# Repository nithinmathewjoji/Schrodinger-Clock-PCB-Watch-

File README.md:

# Schrödinger Clock - Open Source Smartwatch (Prototype⚠️)

<p align="center">Sponsored By </p>
<p align="center">
  
</p>

*A compact, open-source smartwatch powered by the ESP32-S3-WROOM with real-time clock, battery monitoring, and USB charging.*

---

## 📑 Index

1. [Introduction](#introduction)
2. [Features](#features)
3. [Hardware Overview](#hardware-overview)
4. [Sponsorship and Support](#Sponsorship-and-Support)
5. [Schematic & PCB Design](#schematic--pcb-design)
6. [Known issues & Fix](#Known-issues-and-Fix)
7. [Bill of Materials (BoM)](#bill-of-materials-bom)
8. [Firmware & Software](#firmware--software)
9. [Assembly & Soldering Guide](#assembly--soldering-guide)
10. [Usage Guide](#usage-guide)
11. [Power Management](#power-management)
12. [Downloads](#downloads)
13. [Firmware](#firmware)
14. [Visit Interactive BOM](https://nithinmathewjoji.github.io/Schrodinger-Clock-PCB-Watch-/)
15. [Contributing](#contributing)
16. [License](#license)
17. [Acknowledgments](#acknowledgments)

---

## Introduction

The **Schrödinger Watch** is an ESP32-S3-based open-source smartwatch designed with a focus on **compact PCB layout**, **low power consumption**, and **modular features**. It integrates **RTC, I2C display, battery monitoring**, and a **USB charging circuit**, making it a versatile platform for wearable tech enthusiasts.

---

## Features

| Feature                  | Description |
|--------------------------|-------------|
| **Microcontroller**      | ESP32-S3-WROOM (40-pin) |
| **Display**              | I2C OLED |
| **RTC Module**          | DS3231 (with alarm) |
| **Buttons**              | 3 push buttons (pull-up) |
| **Buzzer**               | Included for alarms and notifications |
| **Battery**              | 3.7V Li-Po battery |
| **Charging Circuit**     | TP4056 for Li-Po charging |
| **Battery Monitoring**   | Voltage divider for ADC measurement |
| **USB Communication**    | CP2102 USB programmer |
| **Power Switching**      | *P-MOSFET for auto power control |
| **Protection Circuit**   | Schottky diode for USB protection |

* *feature will be added on the next revision
---

## Hardware Overview

The smartwatch is designed with **SMD components** for compactness. Below is the pin mapping:

| Component   | ESP32 GPIO | Function |
|------------|------------|----------|
| OLED SDA   | GPIO 20   | I2C SDA  |
| OLED SCL   | GPIO 21   | I2C SCL  |
| RTC SDA   | GPIO 20   | I2C SDA  |
| RTC SCL   | GPIO 21   | I2C SCL  |
| RTC Alarm  | GPIO 11 | SQW/INT to ESP32 |
| Battery ADC | GPIO7 | Voltage divider to ESP32 Analog Pin |
| LED        | GPIO 2    | Status Indication |
| LED        | GPIO 3    | Status Indication |
| LED        | GPIO 4    | Status Indication |
| Push Button 1 | GPIO 12  | User Input |
| Push Button 2 | GPIO 13 | User Input |
| Push Button 3 | GPIO 22  | User Input |

* refer circuit  [Schrödinger_Watch_schematics](https://github.com/nithinmathewjoji/Schrodinger-Clock-PCB-Watch-/blob/master/Schematics/schematic.pdf) for more detailed pin out.and pin assignments

---

## Sponsorship and Support

<p align="center">
  
</p>

### 🙏 Thank You, PCBWay!

This project was proudly sponsored by [**PCBWay**](https://pcbway.com/g/D6Z94Y).  

Their support in fabricating the custom PCB for the Schrödinger Watch has been invaluable. The quality, precision, and delivery speed were exceptional — and I’m extremely grateful for their contribution to the maker and open-source community.

If you're looking for reliable PCB prototyping, assembly, or 3D printing services, I highly recommend [**PCBWay**](https://pcbway.com/g/D6Z94Y).

## Schematic & PCB Design

The Schrödinger Watch PCB was designed using **KiCad**. The schematic consists of:
- ESP32-S3-WROOM microcontroller
- RTC DS3231 with backup battery support
- Power management with TP4056 and P-MOSFET
- I2C OLED display
- Battery voltage detection circuit
- USB programmer (CP2102)

**PCB Highlights:**
- **2-layer compact design**
- **Optimized power trace routing**
- **Thermal relief for heat dissipation**
- **Dedicated test points for debugging**

---

## Known issues and Fix

Schrödinger Watch ⌚ – ESP32-S3 DIY Smartwatch

This is the **Schrödinger Watch**, a DIY smartwatch powered by the **ESP32-S3-WROOM**. It's a fully open-source hardware project, designed and assembled from scratch, with a focus on learning, hacking, and creativity.

> ⚠️ **Note:** This is **Rev 1** of the hardware. While functional, it contains some known hardware issues listed below. A refined **Rev 2** is under development and will be released by **September 2025** with additional features and improved reliability.

These are hardware issues identified after assembly and testing:

1. **Missing CE Connection on TP4056:**
   - ⚠️ The CE (Chip Enable) pin was left floating, causing the charging IC to remain disabled.
   - ✅ *Fix:* A patch wire has been added to tie CE to GND manually.

2. **AMS1117 3.3V LDO Lacks Input/Output Capacitors:**
   - ⚠️ Without these caps, voltage regulation is unstable (outputting ~2.4V instead of 3.3V).
   - ✅ *Fix:* Patch capacitors (10µF input, 22µF output) have been manually added close to the LDO pins.

3. **No Pull-Down Resistors for Pushbuttons:**
   - ⚠️ Causes GPIO pins to float, leading to erratic behavior.
   - ✅ *Fix:* External 10kΩ pull-down resistors were added to stabilize the inputs.

4.  **Soldering Considerations:**
   - The board is fully designed with **SMD components** for a compact layout.
   - All components were **hand-soldered** using a soldering iron, without hot air or reflow equipment. Minor imperfections exist, but the board is fully functional.

---

#  What's Coming in Rev 2 (ETA: September 2025)

Rev 2 will be a major update with all hardware issues addressed and new features, including:

- ✅ Proper power rail decoupling and CE management
- ✅ Integrated **MPU6050** IMU for motion sensing
- ✅ Improved button input system
- ✅ Compact routing 
- ✅ Better power management and battery indication
- ✅ Optional haptic feedback (planned)
- ✅ Additional user-customizable GPIOs

 📌 Disclaimer

This is a learning-oriented DIY project and should not be considered a finished consumer product. Use with care and contribute to make it better!

##  Bill of Materials (BoM)

| Component | Quantity | Specification |
|-----------|----------|--------------|
| ESP32-S3-WROOM | 1 | 40-pin module |
| OLED Display | 1 | I2C, 128x64 |
| DS3231 RTC | 1 | Real-time clock module |
| Li-Po Battery | 1 | 3.7V, 500mAh |
| TP4056 Module | 1 | Battery charger |
| CP2102 | 1 | USB-to-serial |
| Buzzer | 1 | 3V piezo |
| Push Buttons | 3 | Momentary switch |
| Resistors & Capacitors | Various | SMD components |

---

##  Firmware & Software

The firmware is written in **Arduino** using the ESP32 library. It supports:
- RTC time synchronization
- OLED display updates
- Battery monitoring
- Button interactions
- Alarm system with buzzer

---

##  Assembly & Soldering Guide

### Tools Required:
- Soldering iron with fine tip
- SMD soldering paste
- Hot air reflow station (optional)
- Multimeter for testing

### Assembly Steps:
1. Solder the **ESP32-S3-WROOM** module first.
2. Attach **RTC DS3231** and connect alarm pin to ESP32.
3. Solder **resistors, capacitors, and power circuits**.
4. Mount **OLED display** and ensure I2C connectivity.
5. Connect **battery and charging module**.
6. Flash firmware and test.

---

##  Usage Guide

### Powering On:
Press and hold the power button. The watch will display the **time, battery status**, and active alarms.

### Setting Time:
Use the **serial monitor** to set the time in RTC using `setTime()`.

### Battery Monitoring:
Battery percentage is displayed on-screen and can be accessed through the serial monitor.

### Alarm Function:
The RTC alarm triggers a buzzer sound at the set time.

---

##  Power Management

- **Automatic Power Switching:** P-MOSFET allows seamless switching between USB and battery.
- **USB Protection:** Schottky diode prevents reverse current flow.
- **Low Power Mode:** ESP32 enters deep sleep when inactive to conserve power.

---

## Downloads
-  **Download KiCad files:** [Schrödinger_Watch.kicad_pcb](https://github.com/nithinmathewjoji/Schrodinger-Clock-PCB-Watch-/tree/master/KiCAD-Files)
-  **Download Code:** [Schrödinger_Watch.ino](path_to_file)
-  **Schematics:** [Schrödinger_Watch_schematics](https://github.com/nithinmathewjoji/Schrodinger-Clock-PCB-Watch-/blob/master/Schematics/schematic.pdf)

---

## Firmware

🛠️ Libraries Used

- [U8g2](https://github.com/olikraus/u8g2)
- [RTClib](https://github.com/adafruit/RTClib)

Install via Arduino Library Manager or PlatformIO.

🚧 Known Hardware Issues (Rev 1)

- ❌ No CE connection to TP4056 (manually patched)
- ❌ No input/output capacitors on MIC39100/AMS1117 LDO (caused unstable voltage)
- ❌ No pull-down resistors for switches (using `INPUT_PULLDOWN` in firmware)

The current version of the firmware is a minimal working build to demonstrate the core functionality of the Schrödinger Watch. Several features are not yet implemented:

- ❌ Push Buttons are read but not interfaced with any logic or user interaction yet.
- ❌ RTC Alarm Interrupt is connected (GPIO 11), but not yet used in the firmware.
- ❌ ESP32 Deep Sleep functionality is not implemented.

These features will be added in the next firmware updates as part of the development toward Rev 2 and in between the current development , revision 2 of this watch expected by September 2025.

# 💾 Firmware Code

```cpp
#include <Wire.h>
#include <U8g2lib.h>
#include <RTClib.h>

// this code works but to be honest there is a lot of places to improve , like switch are just interfaced but not given any function , but can be done like to set time etc etc ......
// all issues will be fixed as a progress please bare with me , but if you have the knowledge then happy to recieve help 

// I2C Pins
#define SDA_PIN 20
#define SCL_PIN 21

// GPIO Definitions
#define LED_PIN       2
#define BATTERY_ADC   7
#define RTC_ALARM_PIN 11

#define BUTTON1 12
#define BUTTON2 13
#define BUTTON3 14

U8G2_SSD1306_128X64_NONAME_F_HW_I2C u8g2(U8G2_R0, U8X8_PIN_NONE);
RTC_DS3231 rtc;

void setup() {
  Serial.begin(115200);

  Wire.begin(SDA_PIN, SCL_PIN);
  u8g2.begin();

  pinMode(LED_PIN, OUTPUT);
  pinMode(RTC_ALARM_PIN, INPUT);
  pinMode(BATTERY_ADC, INPUT);

  pinMode(BUTTON1, INPUT_PULLDOWN);
  pinMode(BUTTON2, INPUT_PULLDOWN);
  pinMode(BUTTON3, INPUT_PULLDOWN);

  if (!rtc.begin()) {
    u8g2.clearBuffer();
    u8g2.setFont(u8g2_font_ncenB08_tr);
    u8g2.drawStr(0, 20, "RTC Not Found");
    u8g2.sendBuffer();
    while (1);
  }

  if (rtc.lostPower()) {
    rtc.adjust(DateTime(F(__DATE__), F(__TIME__)));
  }

  u8g2.clearBuffer();
  u8g2.setFont(u8g2_font_6x10_tr);
  u8g2.drawStr(0, 10, "Schrodinger Watch");
  u8g2.sendBuffer();
  delay(1000);
}

void loop() {
  DateTime now = rtc.now();

  char timeStr[9];
  sprintf(timeStr, "%02d:%02d:%02d", now.hour(), now.minute(), now.second());

  float batteryVoltage = analogRead(BATTERY_ADC) * (3.3 / 4095.0) * 2;  // Adjust based on divider
  char voltStr[10];
  dtostrf(batteryVoltage, 4, 2, voltStr);

  u8g2.clearBuffer();
  u8g2.setFont(u8g2_font_logisoso38_tr);
  u8g2.drawStr(0, 50, timeStr);
  u8g2.setFont(u8g2_font_6x10_tr);
  u8g2.drawStr(0, 62, ("BAT: " + String(voltStr) + "V").c_str());
  u8g2.sendBuffer();

  digitalWrite(LED_PIN, !digitalRead(LED_PIN)); 

  if (digitalRead(BUTTON1)) Serial.println("Button 1 Pressed");
  if (digitalRead(BUTTON2)) Serial.println("Button 2 Pressed");
  if (digitalRead(BUTTON3)) Serial.println("Button 3 Pressed");

  delay(1000);
}
```
##  Contributing

We welcome contributions! If you’d like to improve the watch, please:
1. Fork the repository.
2. Create a new branch.
3. Submit a Pull Request with details.

---

##  License

This project is licensed under the **MIT License**. Feel free to use, modify, and distribute it with proper attribution.

---

## Acknowledgments

Special thanks to the **open-source hardware community** for inspiring this project!

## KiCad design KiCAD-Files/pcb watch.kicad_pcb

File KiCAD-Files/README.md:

## KiCAD files
-  this has the full downloadable project file , you can modify and edit them as you like

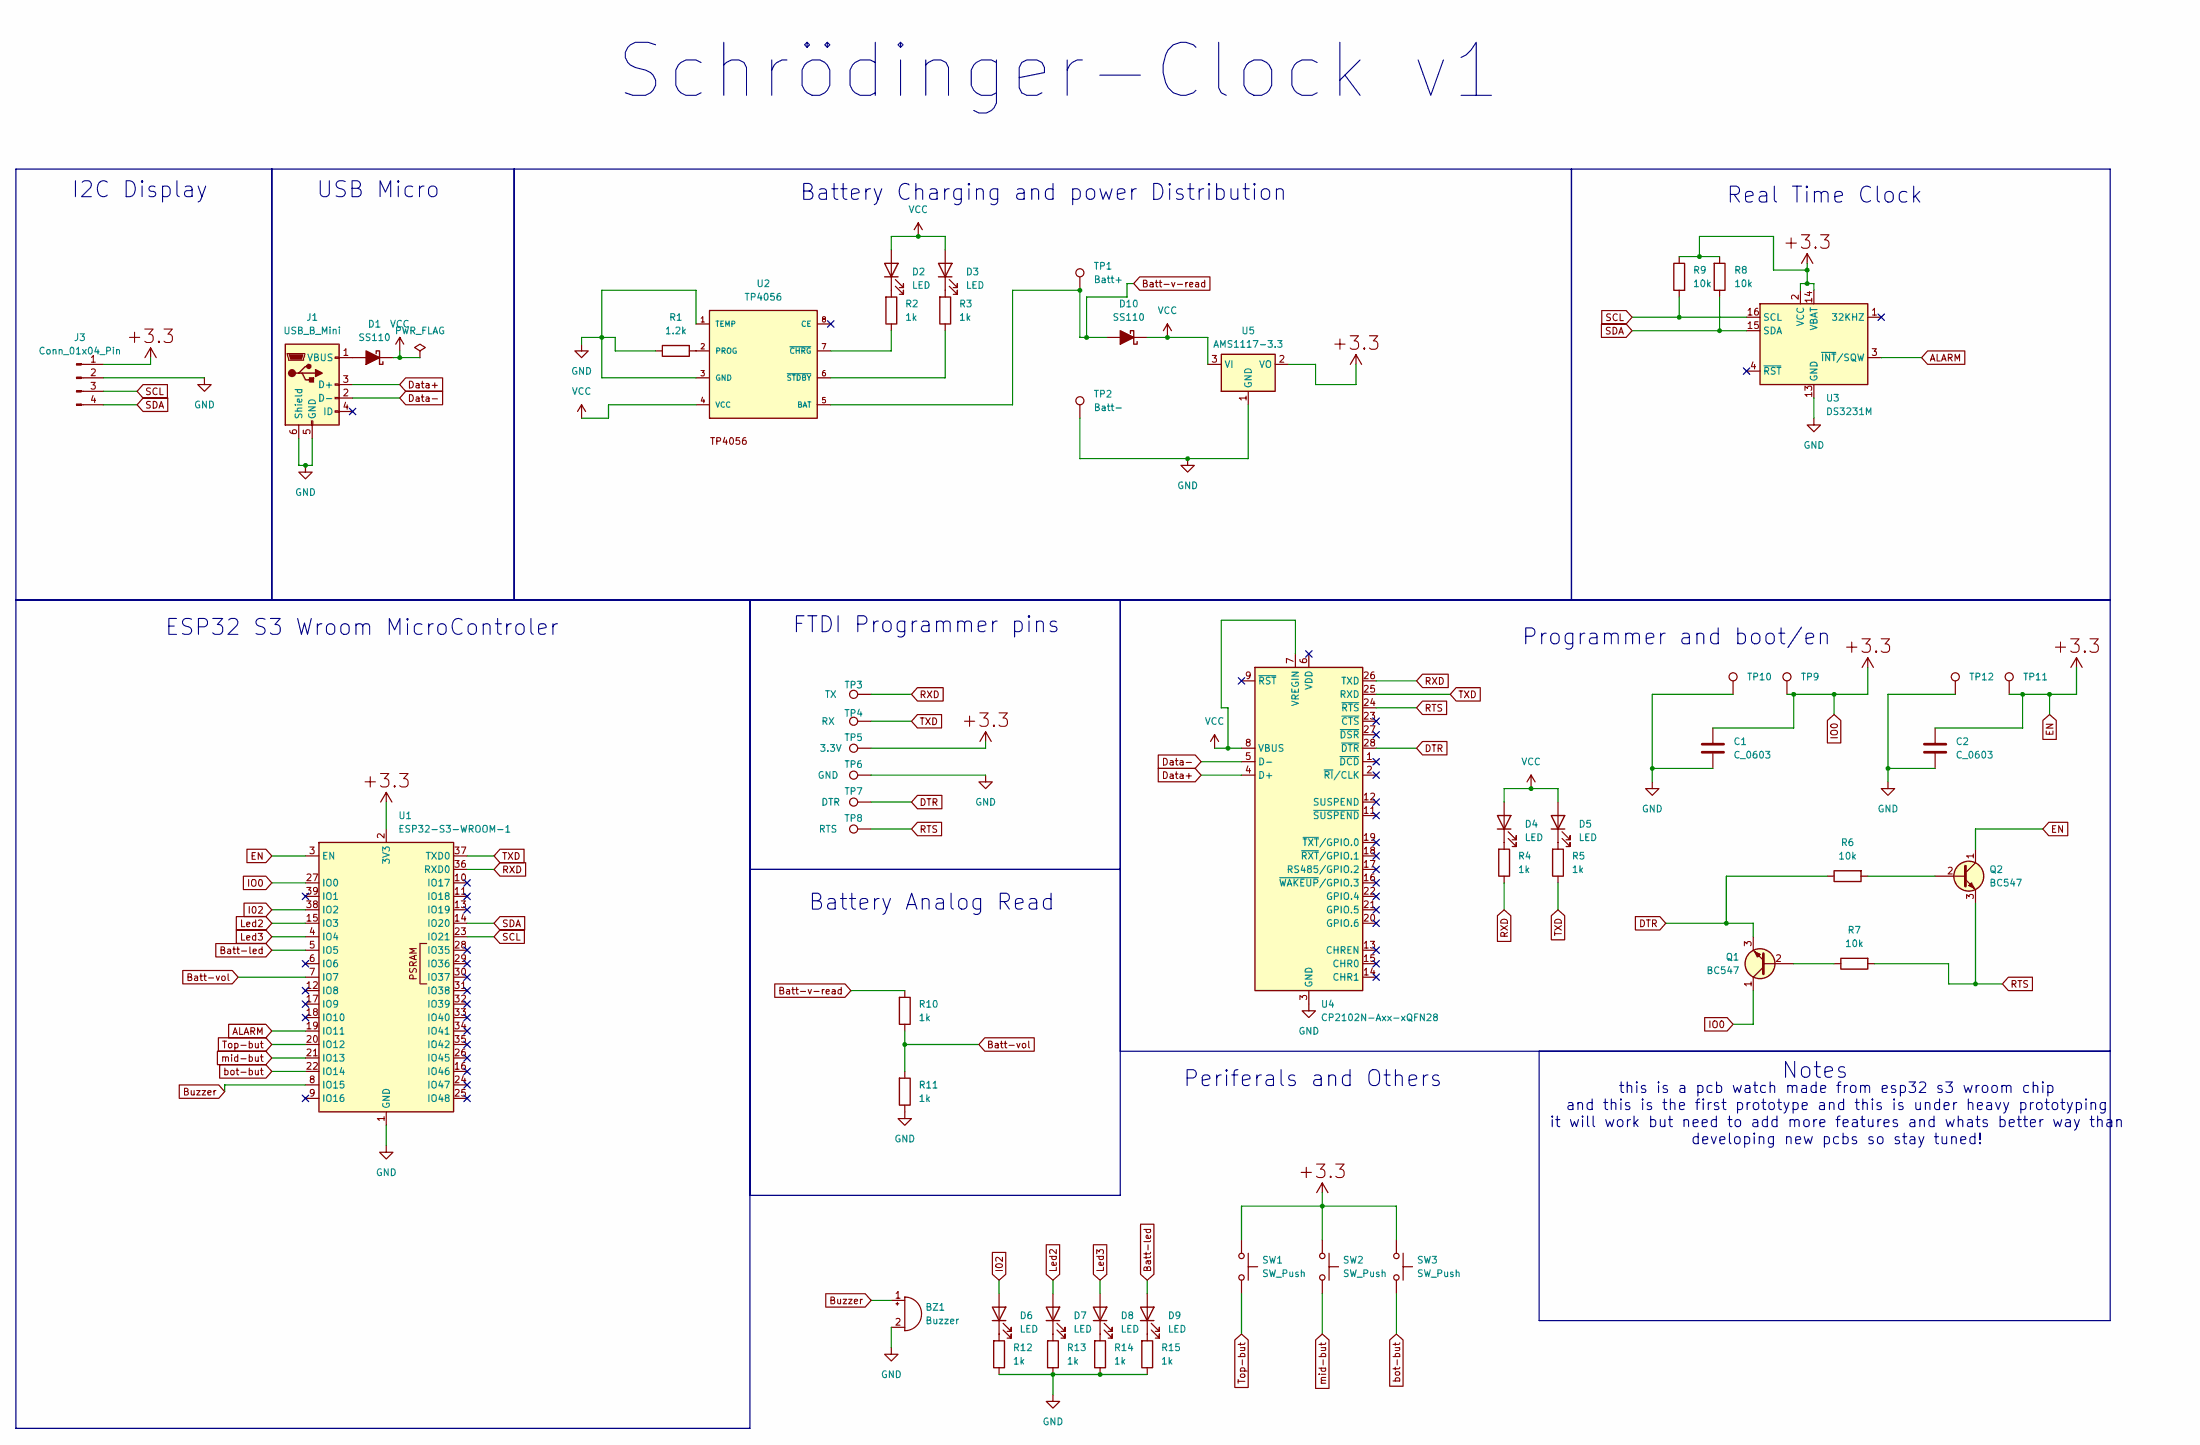
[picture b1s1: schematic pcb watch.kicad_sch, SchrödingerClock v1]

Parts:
BZ1: Buzzer; Buzzer_CUI_CPT-9019S-SMT
C1, C2: C_0603
D1, D10: SS110; D_SMA
D2, D3, D4, D5, D6, D7, D8, D9: LED; LED_0603_1608Metric
J1: USB_B_Mini; USB_Micro-B_Molex-105017-0001
J3: Conn_01x04_Pin; PinHeader_1x04_P2.00mm_Vertical
Q1, Q2: BC547; SOT23-3_PO213
R1: 1.2k; R_0603_1608Metric
R2, R3, R4, R5, R10, R11, R12, R13, R14, R15: 1k; R_0603_1608Metric
R6, R7, R8, R9: 10k; R_0603_1608Metric
SW1, SW2, SW3: SW_Push; SKRK
TP1: Batt+; TestPoint_Pad_D1.0mm
TP2: Batt-; TestPoint_Pad_D1.0mm
TP3: TX; TestPoint_Pad_D1.0mm
TP4: RX; TestPoint_Pad_D1.0mm
TP5: 3.3V; TestPoint_Pad_D1.0mm
TP6: GND; TestPoint_Pad_D1.0mm
TP7: DTR; TestPoint_Pad_D1.0mm
TP8: RTS; TestPoint_Pad_D1.0mm
TP9, TP10, TP11, TP12: push button test points; TestPoint_Pad_D1.0mm
U1: ESP32-S3-WROOM-1
U2: TP4056; SOT23-8
U3: DS3231M; SOIC-16W_7.5x10.3mm_P1.27mm
U4: CP2102N-Axx-xQFN28; QFN-28-1EP_5x5mm_P0.5mm_EP3.35x3.35mm
U5: AMS1117-3.3; SOT-223-3_TabPin2

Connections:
ALARM: U1.19 (IO11), U3.3 (~INT/SQW)
Batt-led: D9.2 (A), U1.5 (IO5)
Batt-v-read: D10.2 (A), R10.1, TP1.1, U2.5 (BAT)
Batt-vol: R10.2, R11.1, U1.7 (IO7)
Buzzer: BZ1.1 (+), U1.8 (IO15)
DTR: Q1.3 (E), R6.2, TP7.1, U4.28 (~DTR)
Data+: J1.3 (D+), U4.4 (D+)
Data-: J1.2 (D-), U4.5 (D-)
EN: C1.1, C2.1, J3.1, Q1.1 (C), Q2.1 (C), R8.1, R9.2, SW1.1, SW2.1, SW3.1, TP5.1, TP9.1, TP11.1, U1.2 (3V3), U1.3 (EN), U1.27 (IO0), U3.2 (VCC), U3.14 (VBAT), U5.2 (VO)
GND: BZ1.2 (-), C1.2, C2.2, J1.5 (GND), J1.6 (Shield), J3.2, R1.2, R11.2, R12.2, R13.2, R14.2, R15.2, TP2.1, TP6.1, TP10.1, TP12.1, U1.1 (GND), U1.40 (GND), U1.41 (GND), U2.1 (TEMP), U2.3 (GND), U3.5 (GND), U3.6 (GND), U3.7 (GND), U3.8 (GND), U3.9 (GND), U3.10 (GND), U3.11 (GND), U3.12 (GND), U3.13 (GND), U4.3 (GND), U4.29 (GND), U5.1 (GND)
I02: D6.2 (A), U1.38 (IO2)
Led2: D7.2 (A), U1.15 (IO3)
Led3: D8.2 (A), U1.4 (IO4)
unnamed: D1.2 (A), J1.1 (VBUS)
unnamed: D2.1 (K), R2.1
unnamed: D3.1 (K), R3.1
unnamed: D4.1 (K), R4.1
unnamed: D5.1 (K), R5.1
unnamed: D6.1 (K), R12.1
unnamed: D7.1 (K), R13.1
unnamed: D8.1 (K), R14.1
unnamed: D9.1 (K), R15.1
unnamed: Q1.2 (B), R7.2
unnamed: Q2.2 (B), R6.1
unnamed: R1.1, U2.2 (PROG)
unnamed: R2.2, U2.7 (~CHRG)
unnamed: R3.2, U2.6 (~STDBY)
RTS: Q2.3 (E), R7.1, TP8.1, U4.24 (~RTS)
RXD: R4.2, TP3.1, U1.36 (RXD0), U4.26 (TXD)
SCL: J3.3, R9.1, U1.23 (IO21), U3.16 (SCL)
SDA: J3.4, R8.2, U1.14 (IO20), U3.15 (SDA)
TXD: R5.2, TP4.1, U1.37 (TXD0), U4.25 (RXD)
Top-but: SW1.2, U1.20 (IO12)
VCC: D1.1 (K), D2.2 (A), D3.2 (A), D4.2 (A), D5.2 (A), D10.1 (K), U2.4 (VCC), U4.7 (VREGIN), U4.8 (VBUS), U5.3 (VI)
bot-but: SW3.2, U1.22 (IO14)
mid-but: SW2.2, U1.21 (IO13)

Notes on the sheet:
this is a pcb watch made from esp32 s3 wroom chip and this is the first prototype and this is under heavy prototyping it will work but need to add more features and whats better way than developing new pcbs so stay tuned!
ESP32 S3 Wroom MicroControler
Periferals and Others
Battery Charging and power Distribution
Schrödinger-Clock v1
Programmer and boot/en
USB Micro
I2C Display
FTDI Programmer pins
Notes
Battery Analog Read
Real Time Clock

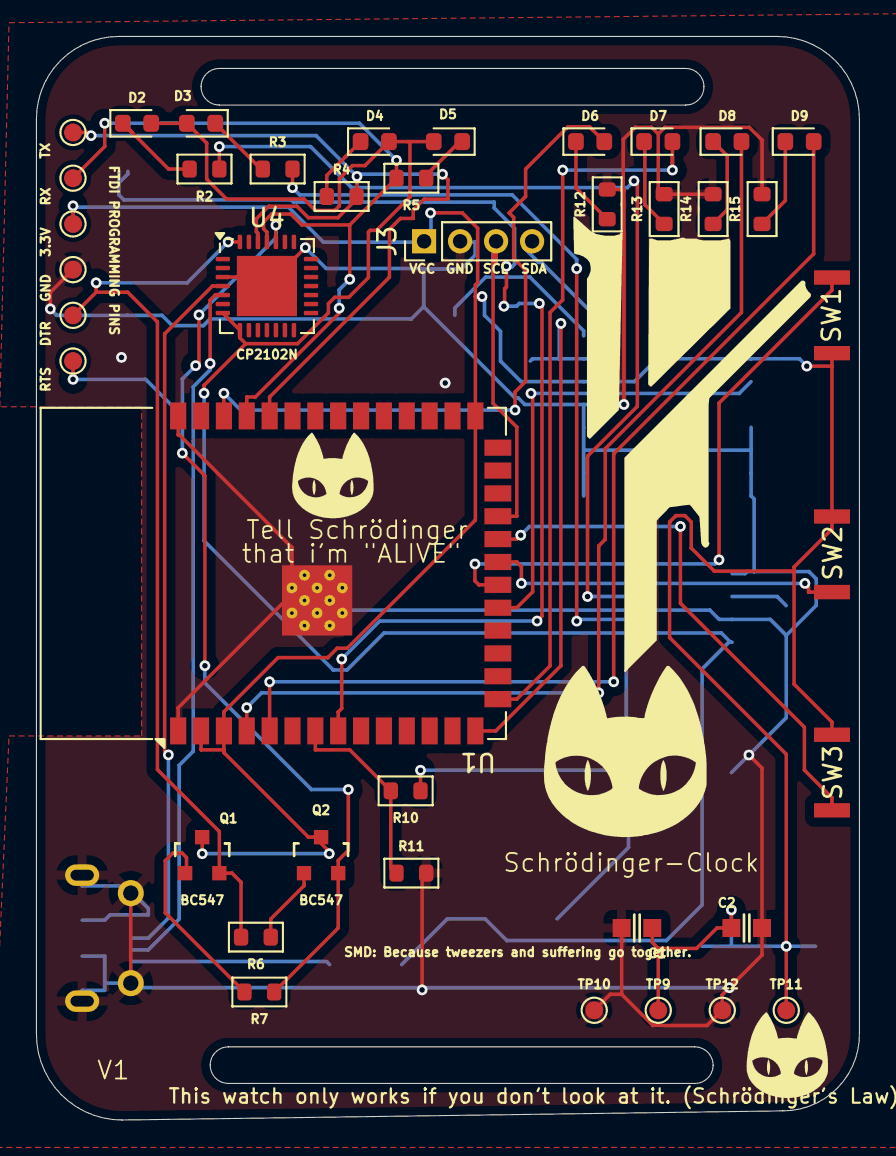
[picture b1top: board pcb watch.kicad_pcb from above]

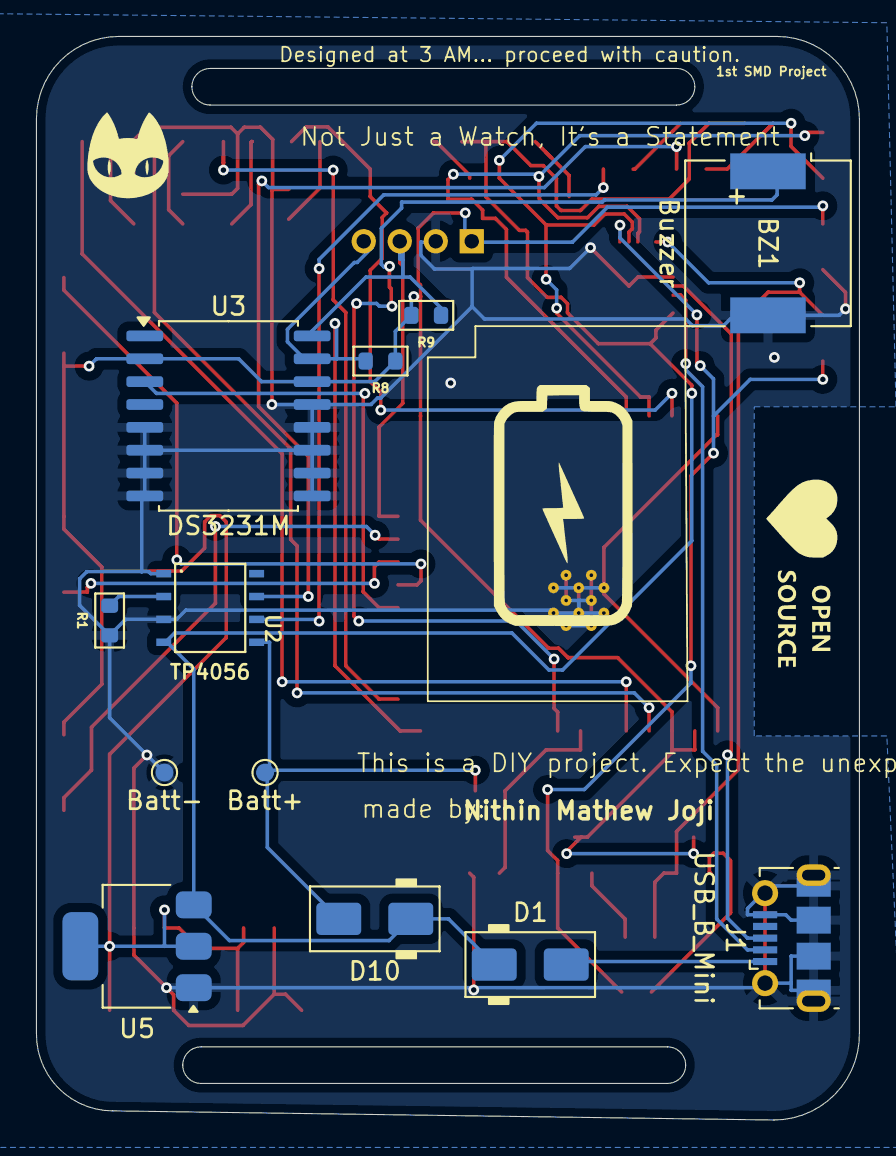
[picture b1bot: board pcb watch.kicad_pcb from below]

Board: 2 copper layers, 45.7 x 60.2 mm, 58 parts (15 on the bottom side), 36 nets.

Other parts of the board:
L1, L1#2, L3: LOGO; catlogo10x13
L2: LOGO; battery
L4: LOGO; catlogo
l6: LOGO; opensource

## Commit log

2025-03-02 changed the mistake in readme file
2025-03-02 Update issue templates
2025-04-11 uploaded the pcb images
2025-04-17 added sponsorship partner logo
2025-04-27 bug fix
    corrected the mistake in schematic, and edited readme
2025-04-29 Update README.md
    added Known issues & Fix
2025-04-29 Update README.md
    added Known issues & Fix and added version 2 expected features
2025-04-30 Update README.md
    edited a small mistake
